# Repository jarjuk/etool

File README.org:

#+PROPERTY: header-args+ :var  ETOOL_DOCKER_TAG="9"
* marcus2002/etool - Docker mapping Gerber files to gcode with simulator support
:PROPERTIES:
:TOC:      :include all
:END:

 ~marcus2002/etool~ - a tool for mapping Gerber files, or image files,
 to gcode for CNC machining and for laser engraving. Provides [[https://linuxcnc.org/][linuxcnc]]
 -simulator for validating CNC execution paths.

:CONTENTS:
- [[#marcus2002etool---docker-mapping-gerber-files-to-gcode-with-simulator-support][marcus2002/etool - Docker mapping Gerber files to gcode with simulator support]]
  - [[#features][Features]]
  - [[#usage][Usage]]
  - [[#architecture][Architecture]]
  - [[#configuration-files-initialized-in-etool-directory][Configuration files initialized in etool directory]]
  - [[#installing-and-using--marcus2002etool][Installing and using  marcus2002/etool]]
    - [[#install-system-tools][Install system tools]]
      - [[#ubuntulinux][Ubuntu/Linux]]
      - [[#windows-10][Windows 10]]
      - [[#install-macos][Install MacOs]]
    - [[#pull-etool-docker-from-dockerio-repo][Pull etool Docker from docker.io repo]]
    - [[#running-etool][Running etool]]
  - [[#example-etool--workflow][Example etool -workflow]]
  - [[#default-cam-parameters][Default CAM parameters]]
    - [[#carving-cut-width-and-cut-depth][Carving cut width and cut depth]]
    - [[#carving-overlap][Carving overlap]]
  - [[#additional-cam-parameters][Additional CAM parameters]]
    - [[#3-grooves][3-grooves]]
  - [[#user-specific-cam-configuration][User specific CAM configuration]]
  - [[#example-projects][Example projects]]
  - [[#development][Development]]
  - [[#release--notes][RELEASE -notes]]
:END:

** Features

 - [X] Tools packaged into the Docker container
   - [X] [[https://github.com/pcb2gcode/pcb2gcode%20][pcb2gcode]] : Tool for mapping Gerber files to gcode
   - [X] [[https://www.linuxcnc.org/docs/2.4/html/gui_image-to-gcode.html][image-to-gcode]]: Tool to convert image to gcode
   - [X] [[https://linuxcnc.org/][linuxcnc]]: Simulator for validating CNC execution paths
   - [X] [[file:docker/etool/etool.sh][etool.sh]]: Simple bash script for managing configuration and
     diretory structures
 - [X] Workflow for processing gerbers
   - [X] Gerber input:
     - [X] Input example project Gerber files
     - [X] Accept project Gerber files from [[https://www.kicad.org/][Kicad EDA -tool]]
     - [X] Proviso for accepting project Gerber files from EDA tools using
       [[file:docker/etool/pcb2gcode-control.template][different naming scheme]]
   - [X] gerber -command
     - [X] converting project Gerger files to gcode
       - [X] [[file:docker/etool/pcb2gcode.ini][opinionated subset]] of ~pcb2gcode~ configurations for
         initialize configuration (possible to add other [[https://github.com/pcb2gcode/pcb2gcode/wiki][~pcb2gcode~ CLI
         configuration options]])
       - [X] set ~pcb2gcode~  autolevelling [on/off]
     - [X] converting Gerber files to png files for laser engraving
       - [X] Front and Back silk gerber layers converted to PNG -files
       - [X] Back silk images flopped around from  mirror position
   - [X] [[file:docker/etool/pcb2gcode-control.template][Gcode output]]:
     - [X] Front, Back, EdgeCut, PTH drill, NPTH drill -gcode files
     - [X] Scrit to create alignment drilling PTH-ALIGN.ngc from PTH.nfc
 - [X] Workflow for processing images
   - [X] Raster image (e.g. png)
   - [X] image -command mapping grey scale value 0..255 to gcode depth carving
 - [X] simulator -command for validating Gcode output
 - [X] Configuration management
   - [X] almost 'zero configuration' - requiring one empty, writable data directory
   - [X] directory structure and configurations automagically
     intialized in an empty data directory
   - [X] intialized configuration not overridden (=possible for user
     to modify initialized configuration)
   - [X] User specific CAM -configuration

** Usage

Command line usage
#+BEGIN_SRC bash :eval no-export :results output :results output :exports results
./etool.sh
#+END_SRC

#+RESULTS:
#+begin_example

         marcus2002/etool:9

         A tool for mapping Gerber/image files to gcode for CNC
         machining and launching linuxcnc -simulator for validating
         CNC execution paths.

         Usage:

         docker DOCKER_OPTS run marcus2002/etool CMD_AND_OPTIONS ...

         where CMD_AND_OPTIONS one of follwoing operations:
         o gerber PROJECT [USER] : create gcode for PROJECT Gerber -files into /etool/02-ngc -dir
                                   and png image files for laser engraving into /etool/02-silk -dir.
                                   USER -specific cam parameters replace default paramerters
                                   (/etool/pcb2gcode.ini, /etool/pcb2gcode-control.template)
         o adrill PROJECT        : convert PTH -drill file to alignement PTH-ALIGN drill file,
                                   used for two sided boards in /etool/02-ngc -dir
         o simulator             : start 'linuxcnc'

         or image cam operation:
         o image IMAGE           : convert IMAGE in /etool/01-image to gcode into /etool/02-ngc 

         or one of data management utilities:
         o ls                    : list data files in /etool -data directories
         o cleanup               : remove files from /etool -data directories
                                   /etool/01-gerber, /etool/01-image, /etool/02-ngc, and /etool/02-silk
         o example TYPE PROJECT  : copy example PROJECT of TYPE input directory
                                   TYPE is 'gerber' or 'image', with respective input direcotories
                                   01-gerber and 01-image

         or one of miscallaneous commands:
         o --help                : this help text
         o usage                 : workflow example (w. example of multiple commands on one line)
         o gerber-help           : help on pcb2gcode options to put into
                                   /etool/pcb2gcode.ini -file and open image explaining
                                   dimension options
         o releases              : output RELEASES document
         o Dockerfile            : show Dockerfile used

         and DOCKER_OPTS options for 'docker run' -command, particularly
         o --rm                             : cleanup after Docker finished
         o --user $(id -u):$(id -g)         : user credentials (instead of root)
         o -e DISPLAY=unix:0                : allow Docker to open X11 apps
         o -v /tmp/.X11-unix:/tmp/.X11-unix : allow Docker to open X11 apps
         o -v HOSTD:/etool                  : data directory HOSTD (must exist,
                                              owned by --user), structure is initialized
         
         Example usage:

         mkdir $HOME/.etool             # create working directory

         export ETOOL='docker run --rm --user 1000:1000 -e DISPLAY=unix:0 -v /tmp/.X11-unix:/tmp/.X11-unix -v $HOME/.etool:/etool marcus2002/etool:9'

         $ETOOL cleanup                 # clean working directories
         $ETOOL ls                      # empty directories
         $ETOOL example gerber soic     # init example 'soic'
         $ETOOL ls                      # expect to see directory /etool/01-gerber populated
         $ETOOL gerber soic             # create gCode for project 'soic'
         $ETOOL adrill soic             # create gcode for alignment create for project 'soic'
         $ETOOL simulator               # start linuxcnc for simulating gcode

         The commands can be given as a one-liner. For example, for the command above:

         $ETOOL cleanup ls example gerber soic ls gerber soic --  adrill soic simulator
         
         Notice! Separator '--' in cam -command signals end of optional parameters
#+end_example

** Architecture

Following box and line diagram gives an overview of ~marcus2002/etool~
-architecture. It presents,

1) *etool -directory*, in which docker ~marcus2002/etool~ initializes
   subdirectory structure and configurations. These configurations are
   accessed by the tools packaged within the container. Configuration
   files are documentend in the following chapter.

2) Gerber to gcode conversion

   1) Gerber files in *01-gerber* subdirectory. These files are
      created using plot command in KiCAD EDA -tool, or using
      ~example~ -command in ~marcus2002/etool~.

   2) Output produced with ~gerber~ -command in ~marcus2002/etool~:
      gcode files in *02-ngc* subdirectory.

   3) Output produced with ~gerber~ -command in ~marcus2002/etool~:
      png files for front and back Gerber -layers in *01-silk*
      subdirectory.

3) Image to gcode conversion

   1) Image files in *01-image* subdirectory. These files are created
      using drawing tool e.g. inkscape.

   2) Output produced with ~image~ -command in ~marcus2002/etool~: gcode
      files in *02-ngc* subdirectory.

4) gcode files in *02-ngc* -subdirectory read by ~linuxcnc~ -simulator
   packaged within in ~marcus2002/etool~ docker container.

5) gcode files in *02-ngc* -subdirectory copied for CNC for milling,
   drilling, and edge cutting.

6) Image files in *02-silk* -subdirectory copied for laser engraving

#+begin_example
                                     +--------------------------------+
                                     | marcus2002/etool -container    |
                                     | - pcb2gcode                    |
        +-----------------+          | - linuxcnc -simulator          |
        | EDA -tool e.g.  |          | - etool.sh -script             |
        | Kicad           |          | - initial configuration        |
        |                 |          +--------------------------------+
        +-----------------+               |     |       ^          ^
                   | +-----------------+  |     |       |          |
                   | | Drawing tool    |  |     |       |          |
                   | | e.g. inkscape   |  |     |       |          |
                   | |                 |  |     |       |          |
                   | +-----------------+  |     |       |          |
             plot  |    |                 |     |       |          |
          command  |    | +---------------+     |       |          |
                   |    | | example command     |       |tool      |
+----------------+ |    | |                init |       |access    | file read
|etool -directory| |    | |                once |       |          | for simulation
|                +-|-- -|-|---------------------|-------|---+      |
|   +--------------+    | |                     V       |   |      |
|   | +-----------------|-+                   configuration |      |
|   | |                 | |                                 |      |
|   | |   +-------------V-V-+        +-----------------+    |      |
|   | |   | 01-image        |        | 02-ngc          |    |      |
|   | |   |                 |  image |                 |-----------+
|   | |   | Image files     |--------> gcode -files    |    |   +-----------------+
|   | |   |                 |  +---->|                 |--------> CNC machine     |
|   | |   +-----------------+  |     +-----------------+    |   | - linuxcnc      |
|   | |                        |                            |   |                 |
|   | |                        |     +-----------------+    |   +-----------------+
| +-V-V-------------+          |     | 02-silk         |    |
| | 01-gerber       | gerber   |     |                 |    |   +-----------------+
| |                 |----------+-----> png -files      |    |   | Laser engraving |
| | Gerber files    |                |                 |------->|                 |
| |                 |                +-----------------+    |   |                 |
| +-----------------+                                       |   +-----------------+
|                                                           |
+-----------------------------------------------------------+

#+end_example

** Configuration files initialized in ~etool directory~

Following table summarizes configuration files initialized under
~etool~ -data directory.

| Configuration file               | Content                                                               |
|----------------------------------+-----------------------------------------------------------------------|
| [[file:docker/etool/pcb2gcode.ini]]  | pcb2gcode -tool CAM parameters  with instructions for 1/2 -sided PCBs |
| [[file:docker/etool/pcb2gcode-control.template][pcb2gcode-control.template]]       | Input/ouput configuration of pcb2gcode -tool                          |
| [[file:docker/etool/axis_etool.ini]] | linuxcnc simulator configuration (w. probe support)                   |

** Installing and using  ~marcus2002/etool~
:PROPERTIES:
:header-args:bash+: :dir  "."
:END:

*** Install system tools

**** Ubuntu/Linux

- Install Docker: https://docs.docker.com/engine/install/ubuntu/
- Post installation steps for Linux: https://docs.docker.com/engine/install/linux-postinstall/

**** Windows 10

- Install Docker Desktop on Windows: https://docs.docker.com/desktop/windows/install/
  - defines Windows features and Bios setting needed to run Docker
  - a hint for the impatient: installer checks that Docker
    prerequisites are met
- Install VcXsrv Windows X Server: https://sourceforge.net/projects/vcxsrv/
  - When launching VcXsrv choose 'disable access control checked' to
    allow Docker to open X11 windows

*Windows 10 problems*:
- linuxcnc simulator machinen preview did not work. Patched
  [[file:etool.cmd]] to set environment variable
  ~LIBGL_ALWAYS_INDIRECT=1~. In spite of this "fix" need to click DRO
  tab to make linuxcnc to refresh machine preview.

**** Install MacOs

- Install Docker Desktop on Mac: https://docs.docker.com/desktop/mac/install/
- Install X11 support on Mac: https://www.xquartz.org/

*MacOs X11 problem*:

Xquartz 2.8.1 may report an error
#+begin_example
libGL error: No matching fbConfigs or visuals found
libGL error: failed to load driver: swrast
#+end_example
which may be solved issuing command
#+begin_example
defaults write org.xquartz.X11 enable_iglx -bool true
#+end_example
and restarting XQuartz again. However, it may be this does not fix the
problem persistently, and XQuartz must be restarted again, after each
X11 session launch.

*** Pull ~etool~ Docker from docker.io repo

Current Docker Tag
#+BEGIN_SRC bash :eval no-export :results output :exports results
echo ETOOL_DOCKER_TAG=$ETOOL_DOCKER_TAG
#+END_SRC

#+RESULTS:
: ETOOL_DOCKER_TAG=9

Pull ~marcus2002/etool:$ETOOL_DOCKER_TAG~ from Docker hub

#+BEGIN_SRC bash :eval no-export :results output :exports both
docker pull marcus2002/etool:$ETOOL_DOCKER_TAG
#+END_SRC

: 9: Pulling from marcus2002/etool
: Digest: sha256:514c385deede32a71bf4e57752d28bf72b0cfdee7802237a1ebd98f3b83d2d6b
: Status: Image is up to date for marcus2002/etool:9
: docker.io/marcus2002/etool:9

: Digest: sha256:8150eb52eb17bf79acf92d8f47bf5e9ff7e0e46fb0d69fa704446388efeb36ee
: Status: Image is up to date for marcus2002/etool:7
: docker.io/marcus2002/etool:7

*** Running etool

To simplify running  ~marcus2002/etool~ two scripts are provided

- [[file:etool.sh]] : Running ~marcus2002/etool~ on Linux
- [[file:etoolMac.sh]] : Running ~marcus2002/etool~ on MacOs
- [[file:etool.cmd]] : Running ~marcus2002/etool~  on Windows

Copy these scripts to a CLI PATH and validate ETOOL_DIR and TAG
variables (change if needed). Validate installation and version with
the command

#+BEGIN_SRC bash :eval no-export :results output :exports both
./etool.sh --version
#+END_SRC

#+RESULTS:
:          marcus2002/etool:7

** Example ~etool~ -workflow

Using data directory ~tmp/etool~ for tesing. Reset directory and
remove old existing directory
#+BEGIN_SRC bash :eval no-export :results output
rm -rf tmp/etool
mkdir -p tmp/etool
#+END_SRC

#+RESULTS:

Use ~<<run-etool>>~ below as a short hand for
#+name: run-etool
#+BEGIN_SRC bash :eval no :results output :exports code
docker run --rm --user $(id -u):$(id -g) -e DISPLAY=unix:0 -v /tmp/.X11-unix:/tmp/.X11-unix -v $(pwd)/tmp/etool:/etool marcus2002/etool:$ETOOL_DOCKER_TAG
#+END_SRC

Calling ~<<run-etool>>~ for the first time inializes directory
structure. Command ~ls~ shows empty directories ~/etool/01-gerber~, 
~/etool/02-ngc~, and ~/etool/02-silk~:

#+BEGIN_SRC bash :eval no-export :results output :noweb yes :exports both
<<run-etool>> ls
#+END_SRC

#+RESULTS:
#+begin_example
Directory /etool/01-gerber created
Directory /etool/01-image created
Directory /etool/02-ngc created
Directory /etool/02-silk created
Directory /etool/linuxcnc/configs/sim.axis created
File /etool/pcb2gcode.ini created
File /etool/linuxcnc/configs/sim.axis/axis_etool.ini created
File /etool/linuxcnc/configs/sim.axis/sim_mm.tbl created
File /etool/pcb2gcode-control.template created
File /etool/.linuxcncrc created
/etool/01-gerber:
total 0

/etool/01-image:
total 0

/etool/02-ngc:
total 0

/etool/02-silk:
total 0
#+end_example

Use ~<<run-etool>>~ to populate example Gerbers for ~soic~ -project:

#+BEGIN_SRC bash :eval no-export :results output :noweb yes :exports both
<<run-etool>> example gerber soic
#+END_SRC

#+RESULTS:
#+begin_example
Directory /etool/01-gerber exits - not modified
Directory /etool/01-image exits - not modified
Directory /etool/02-ngc exits - not modified
Directory /etool/02-silk exits - not modified
Directory /etool/linuxcnc/configs/sim.axis exits - not modified
File /etool/pcb2gcode.ini exits - not modified
File /etool/linuxcnc/configs/sim.axis/axis_etool.ini exits - not modified
File /etool/linuxcnc/configs/sim.axis/sim_mm.tbl exits - not modified
File /etool/pcb2gcode-control.template exits - not modified
File /etool/.linuxcncrc exits - not modified
soic-B_Cu.gbr
soic-B_Mask.gbr
soic-B_Paste.gbr
soic-B_SilkS.gbr
soic-Edge_Cuts.gbr
soic-F_Cu.gbr
soic-F_Mask.gbr
soic-F_Paste.gbr
soic-F_SilkS.gbr
soic-NPTH-drl_map.ps
soic-NPTH.drl
soic-PTH-drl_map.ps
soic-PTH.drl
soic-job.gbrjob
#+end_example

Using ~gerber~-command in ~<<run-etool>>~ for ~soic~ -project to
create gcode files into ~02-ngc~ directory, and png files into
~02-silk~ directory

#+BEGIN_SRC bash :eval no-export :results output :noweb yes :exports both
<<run-etool>> gerber soic
#+END_SRC

#+RESULTS:
#+begin_example
Directory /etool/01-gerber exits - not modified
Directory /etool/01-image exits - not modified
Directory /etool/02-ngc exits - not modified
Directory /etool/02-silk exits - not modified
Directory /etool/linuxcnc/configs/sim.axis exits - not modified
File /etool/pcb2gcode.ini exits - not modified
File /etool/linuxcnc/configs/sim.axis/axis_etool.ini exits - not modified
File /etool/linuxcnc/configs/sim.axis/sim_mm.tbl exits - not modified
File /etool/pcb2gcode-control.template exits - not modified
File /etool/.linuxcncrc exits - not modified
pcb2gcode using configuration files /etool/pcb2gcode-control.template, /etool/pcb2gcode.ini
Importing front side... DONE.
Importing back side... DONE.
Importing outline... DONE.
Processing input files... DONE.
Exporting back... DONE. (Height: 15.1mm Width: 34.1mm)
Exporting front... DONE. (Height: 15.1mm Width: 34.1mm)
Exporting outline... DONE. (Height: 15.1mm Width: 34.1mm) The board should be cut from the FRONT side. 
Importing drill... DONE.
Exporting milldrill... Exporting drill... DONE. The board should be drilled from the FRONT side.
END.
Importing front side... not specified.
Importing back side... not specified.
Importing outline... DONE.
Processing input files... DONE.
Exporting outline... DONE. (Height: 15.1mm Width: 34.1mm) The board should be cut from the FRONT side. 
Importing drill... DONE.
Exporting milldrill... Exporting drill... DONE. The board should be drilled from the FRONT side.
END.
Convert Gerber  /etool/01-gerber/soic-F_SilkS.gbr to png -image /etool/02-silk/soic-F_SilkS.png
Convert Gerber  /etool/01-gerber/soic-B_SilkS.gbr to png -image /etool/02-silk/soic-B_SilkS.png
#+end_example

After ~cam~ command, directory ~/etool/02-ngc~ contains gcode in ~ngc~
-files, and directory ~/etool/02-silk~ ~png~ -files for gerber silk
layers:

#+BEGIN_SRC bash :eval no-export :results output :noweb yes :exports both
<<run-etool>> ls
#+END_SRC

#+RESULTS:
#+begin_example
Directory /etool/01-gerber exits - not modified
Directory /etool/01-image exits - not modified
Directory /etool/02-ngc exits - not modified
Directory /etool/02-silk exits - not modified
Directory /etool/linuxcnc/configs/sim.axis exits - not modified
File /etool/pcb2gcode.ini exits - not modified
File /etool/linuxcnc/configs/sim.axis/axis_etool.ini exits - not modified
File /etool/linuxcnc/configs/sim.axis/sim_mm.tbl exits - not modified
File /etool/pcb2gcode-control.template exits - not modified
File /etool/.linuxcncrc exits - not modified
/etool/01-gerber:
total 112
-rw-r--r-- 1 1000 1000  1953 Jul  4 11:11 soic-B_Cu.gbr
-rw-r--r-- 1 1000 1000  1035 Jul  4 11:11 soic-B_Mask.gbr
-rw-r--r-- 1 1000 1000   541 Jul  4 11:11 soic-B_Paste.gbr
-rw-r--r-- 1 1000 1000 12476 Jul  4 11:11 soic-B_SilkS.gbr
-rw-r--r-- 1 1000 1000   749 Jul  4 11:11 soic-Edge_Cuts.gbr
-rw-r--r-- 1 1000 1000  5874 Jul  4 11:11 soic-F_Cu.gbr
-rw-r--r-- 1 1000 1000  3504 Jul  4 11:11 soic-F_Mask.gbr
-rw-r--r-- 1 1000 1000  3010 Jul  4 11:11 soic-F_Paste.gbr
-rw-r--r-- 1 1000 1000  5682 Jul  4 11:11 soic-F_SilkS.gbr
-rw-r--r-- 1 1000 1000 15377 Jul  4 11:11 soic-NPTH-drl_map.ps
-rw-r--r-- 1 1000 1000   377 Jul  4 11:11 soic-NPTH.drl
-rw-r--r-- 1 1000 1000 27525 Jul  4 11:11 soic-PTH-drl_map.ps
-rw-r--r-- 1 1000 1000   532 Jul  4 11:11 soic-PTH.drl
-rw-r--r-- 1 1000 1000  2491 Jul  4 11:11 soic-job.gbrjob

/etool/01-image:
total 0

/etool/02-ngc:
total 624
-rw-r--r-- 1 1000 1000    412 Jul  4 11:12 original_drill.svg
-rw-r--r-- 1 1000 1000   5311 Jul  4 11:12 outp0_original_back.svg
-rw-r--r-- 1 1000 1000    522 Jul  4 11:12 outp0_original_outline.svg
-rw-r--r-- 1 1000 1000  10814 Jul  4 11:12 outp1_original_front.svg
-rw-r--r-- 1 1000 1000    522 Jul  4 11:12 outp2_original_outline.svg
-rw-r--r-- 1 1000 1000   5312 Jul  4 11:12 outp3_masked_back.svg
-rw-r--r-- 1 1000 1000  10817 Jul  4 11:12 outp4_masked_front.svg
-rw-r--r-- 1 1000 1000  61090 Jul  4 11:12 processed_back.svg
-rw-r--r-- 1 1000 1000  37018 Jul  4 11:12 processed_back_final.svg
-rw-r--r-- 1 1000 1000 109965 Jul  4 11:12 processed_front.svg
-rw-r--r-- 1 1000 1000  68915 Jul  4 11:12 processed_front_final.svg
-rw-r--r-- 1 1000 1000   2192 Jul  4 11:12 processed_outline.svg
-rw-r--r-- 1 1000 1000  29533 Jul  4 11:12 soic-B_Cu.ngc
-rw-r--r-- 1 1000 1000   3707 Jul  4 11:12 soic-Edge_Cuts.ngc
-rw-r--r-- 1 1000 1000  50897 Jul  4 11:12 soic-F_Cu.ngc
-rw-r--r-- 1 1000 1000    737 Jul  4 11:12 soic-NPTH.ngc
-rw-r--r-- 1 1000 1000    902 Jul  4 11:12 soic-PTH.ngc
-rw-r--r-- 1 1000 1000  45335 Jul  4 11:12 traced_back.svg
-rw-r--r-- 1 1000 1000  21263 Jul  4 11:12 traced_back_final.svg
-rw-r--r-- 1 1000 1000  79633 Jul  4 11:12 traced_front.svg
-rw-r--r-- 1 1000 1000  38583 Jul  4 11:12 traced_front_final.svg
-rw-r--r-- 1 1000 1000   1770 Jul  4 11:12 traced_outline.svg

/etool/02-silk:
total 12
-rw-r--r-- 1 1000 1000 4744 Jul  4 11:12 soic-B_SilkS.png
-rw-r--r-- 1 1000 1000 3437 Jul  4 11:12 soic-F_SilkS.png
#+end_example

Soic -project uses two sided PCB layout. To align board in milling,
the PCB design is symmetrical along Y-axis with origin on lower edge
of the PCB board. The design contains two alignement vias on the
Y-axis. First via is in position (0mm,-3mm) and the second is located
on the Y-axis, 3mm above the board top edge on Y=14mm. These vias are
drilled to -4.5mm *into the supporting plane* (= use thick enough
sacrifial plane where PCB is attached to avoid drilling into CNC
table).

The crux of this drilling operation is gcode snippet shown below

#+begin_example
G81 R2.00000  Z-4.5000  F30.00000 X0.00000 Y-3.0000
X0.00000 Y14.00000
G80
#+end_example

To create alignement drilling ~<<run-etool>>~ provides command
~adrill~. 

For example, to create ~PTH-ALIGN.ngc~ for soic project run:

#+BEGIN_SRC bash :eval no-export :results output :noweb yes :exports both
<<run-etool>> adrill soic
#+END_SRC

#+RESULTS:
: PTH_DRILL=/etool/02-ngc/soic-PTH.ngc, ALIGN_DRILL=/etool/02-ngc/soic-PTH-ALIGN.ngc

Command ~ls~ shows new file ~soic-PTH-ALIGN.ngc~ in directory ~02-ngc~:
#+BEGIN_SRC bash :eval no-export :results output :noweb yes :exports both
  <<run-etool>> ls
#+END_SRC

#+RESULTS:
#+begin_example
Directory /etool/01-gerber exits - not modified
Directory /etool/01-image exits - not modified
Directory /etool/02-ngc exits - not modified
Directory /etool/02-silk exits - not modified
Directory /etool/linuxcnc/configs/sim.axis exits - not modified
File /etool/pcb2gcode.ini exits - not modified
File /etool/linuxcnc/configs/sim.axis/axis_etool.ini exits - not modified
File /etool/linuxcnc/configs/sim.axis/sim_mm.tbl exits - not modified
File /etool/pcb2gcode-control.template exits - not modified
File /etool/.linuxcncrc exits - not modified
/etool/01-gerber:
total 112
-rw-r--r-- 1 1000 1000  1953 Jul  4 11:11 soic-B_Cu.gbr
-rw-r--r-- 1 1000 1000  1035 Jul  4 11:11 soic-B_Mask.gbr
-rw-r--r-- 1 1000 1000   541 Jul  4 11:11 soic-B_Paste.gbr
-rw-r--r-- 1 1000 1000 12476 Jul  4 11:11 soic-B_SilkS.gbr
-rw-r--r-- 1 1000 1000   749 Jul  4 11:11 soic-Edge_Cuts.gbr
-rw-r--r-- 1 1000 1000  5874 Jul  4 11:11 soic-F_Cu.gbr
-rw-r--r-- 1 1000 1000  3504 Jul  4 11:11 soic-F_Mask.gbr
-rw-r--r-- 1 1000 1000  3010 Jul  4 11:11 soic-F_Paste.gbr
-rw-r--r-- 1 1000 1000  5682 Jul  4 11:11 soic-F_SilkS.gbr
-rw-r--r-- 1 1000 1000 15377 Jul  4 11:11 soic-NPTH-drl_map.ps
-rw-r--r-- 1 1000 1000   377 Jul  4 11:11 soic-NPTH.drl
-rw-r--r-- 1 1000 1000 27525 Jul  4 11:11 soic-PTH-drl_map.ps
-rw-r--r-- 1 1000 1000   532 Jul  4 11:11 soic-PTH.drl
-rw-r--r-- 1 1000 1000  2491 Jul  4 11:11 soic-job.gbrjob

/etool/01-image:
total 0

/etool/02-ngc:
total 628
-rw-r--r-- 1 1000 1000    412 Jul  4 11:12 original_drill.svg
-rw-r--r-- 1 1000 1000   5311 Jul  4 11:12 outp0_original_back.svg
-rw-r--r-- 1 1000 1000    522 Jul  4 11:12 outp0_original_outline.svg
-rw-r--r-- 1 1000 1000  10814 Jul  4 11:12 outp1_original_front.svg
-rw-r--r-- 1 1000 1000    522 Jul  4 11:12 outp2_original_outline.svg
-rw-r--r-- 1 1000 1000   5312 Jul  4 11:12 outp3_masked_back.svg
-rw-r--r-- 1 1000 1000  10817 Jul  4 11:12 outp4_masked_front.svg
-rw-r--r-- 1 1000 1000  61090 Jul  4 11:12 processed_back.svg
-rw-r--r-- 1 1000 1000  37018 Jul  4 11:12 processed_back_final.svg
-rw-r--r-- 1 1000 1000 109965 Jul  4 11:12 processed_front.svg
-rw-r--r-- 1 1000 1000  68915 Jul  4 11:12 processed_front_final.svg
-rw-r--r-- 1 1000 1000   2192 Jul  4 11:12 processed_outline.svg
-rw-r--r-- 1 1000 1000  29533 Jul  4 11:12 soic-B_Cu.ngc
-rw-r--r-- 1 1000 1000   3707 Jul  4 11:12 soic-Edge_Cuts.ngc
-rw-r--r-- 1 1000 1000  50897 Jul  4 11:12 soic-F_Cu.ngc
-rw-r--r-- 1 1000 1000    737 Jul  4 11:12 soic-NPTH.ngc
-rw-r--r-- 1 1000 1000   1158 Jul  4 11:15 soic-PTH-ALIGN.ngc
-rw-r--r-- 1 1000 1000    902 Jul  4 11:12 soic-PTH.ngc
-rw-r--r-- 1 1000 1000  45335 Jul  4 11:12 traced_back.svg
-rw-r--r-- 1 1000 1000  21263 Jul  4 11:12 traced_back_final.svg
-rw-r--r-- 1 1000 1000  79633 Jul  4 11:12 traced_front.svg
-rw-r--r-- 1 1000 1000  38583 Jul  4 11:12 traced_front_final.svg
-rw-r--r-- 1 1000 1000   1770 Jul  4 11:12 traced_outline.svg

/etool/02-silk:
total 12
-rw-r--r-- 1 1000 1000 4744 Jul  4 11:12 soic-B_SilkS.png
-rw-r--r-- 1 1000 1000 3437 Jul  4 11:12 soic-F_SilkS.png
#+end_example

Use ~simulator~ command to start linuxcnc simulator. Especially,
validate gcode in ~PTH-ALIGN.ngc~ file.

Running

#+BEGIN_SRC bash :eval no-export :results output :noweb yes :exports code
<<run-etool>> simulator
#+END_SRC

#+RESULTS:
: Directory /etool/01-gerber exits - not modified
: Directory /etool/02-ngc exits - not modified
: Directory /etool/linuxcnc/configs/sim.axis exits - not modified
: File /etool/pcb2gcode.ini exits - not modified
: File /etool/linuxcnc/configs/sim.axis/axis_etool.ini exits - not modified
: File /etool/linuxcnc/configs/sim.axis/sim_mm.tbl exits - not modified
: File /etool/pcb2gcode-control.template exits - not modified
: File /etool/.linuxcncrc exits - not modified
: RUN: linuxcnc

opens dialog for configuration selection (Choose ~axis_etool~)

[[file:pics-keep/simulator-conf.png]]

~linuxcnc~ ~File Open~ -command shows gcode files in ~/etool/02-ngc~
-directory

[[file:pics-keep/simulator-open-file.png]]

Finally, ~cleanup~ -command empties data directories, and ~ls~
-command shows that data directories ~/etool/01-gerber~ and
~/etool/02-ngc~ are empty.
#+BEGIN_SRC bash :eval no-export :results output :noweb yes :exports both
<<run-etool>> cleanup ls
#+END_SRC

#+RESULTS:
#+begin_example
Directory /etool/01-gerber exits - not modified
Directory /etool/01-image exits - not modified
Directory /etool/02-ngc exits - not modified
Directory /etool/02-silk exits - not modified
Directory /etool/linuxcnc/configs/sim.axis exits - not modified
File /etool/pcb2gcode.ini exits - not modified
File /etool/linuxcnc/configs/sim.axis/axis_etool.ini exits - not modified
File /etool/linuxcnc/configs/sim.axis/sim_mm.tbl exits - not modified
File /etool/pcb2gcode-control.template exits - not modified
File /etool/.linuxcncrc exits - not modified
/etool/01-gerber:

/etool/01-image:
/etool/01-gerber:
total 0

/etool/01-image:
total 0

/etool/02-ngc:
total 0

/etool/02-silk:
total 0
#+end_example

** Default CAM parameters

*** Carving cut width and cut depth

 #+caption: V -milling bit
 [[file:pics-keep/v-bit2.png]]

 Figure 1 shows geometry for a V -milling bit with tip width ~w~ and
 tip angle ~\alpha~. When using engraving depth ~z~, the resulting
 groove has width of ~cut~.

 #+caption: V -milling bit
 [[file:pics-keep/latex-calc.png]]

 Python script for calculating cut width for V -milling bit with tip
 width ~w~, tip angle ~alpha~, and carving depth ~z~

 #+BEGIN_SRC python :eval no-export :results output :noweb no :session *Python* :exports code
 from  math import tan, radians
 def cutWidth( alpha, w, z):
    cut = 2*tan(radians(alpha)/2)*(w/2/tan(radians(alpha)/2) + z)
    return cut
 #+END_SRC

Using the script above to calculate cut width for V -milling bit
 - with tip angle ~alpha=60 deg~
 - and tip width ~w=0.1 mm~
 - carving into depth ~z=0.1 mm~

 #+name: example1
 #+BEGIN_SRC python :eval no-export :results output :noweb no :session *Python* :exports both
 print( f"cut={cutWidth(alpha=60,w=0.1,z=.1):.4f}")
 #+END_SRC

returns ~cut~ witdh

 #+RESULTS: example1
 : cut=0.2155

Default CAM configuration [[file:docker/etool/pcb2gcode.ini]] defines
carving parameters:

#+BEGIN_SRC bash :eval no-export :results output :exports results
grep -E '^mill-diameters|^zwork' docker/etool/pcb2gcode.ini
#+END_SRC

#+RESULTS:
: zwork=-0.1mm            # milling depth
: mill-diameters=0.2155mm # milling cut

*** Carving overlap

Python script to calculate minimum overlap -% needed to achieve
isolation width $i$ when carving $n$ grooves of width $cut$:

#+BEGIN_SRC python :eval no-export :results output :noweb no :session *Python* :exports code
  def overLap( i, cut, n):
      """:return: (min) overLap -‰ needed to achive isolation 'i' when
      carving 'n' grooves of width 'cut'. None if not possible

      """
      # Max area possible to cover with n cuts
      maxCarvingCover = n*cut

      # Not possible to isolate
      if maxCarvingCover < i: return None

      # Need at least two carvings to have any overLap
      if n < 2: return None
      
      #  width of one overLap 
      overLapWidth = (maxCarvingCover - i)/(n-1)
      
      # one overLap width from cut width as percent
      return overLapWidth / cut * 100.0
#+END_SRC

#+RESULTS:

To achive isolation width ~0.38mm~, when carving ~2~ grooves of width
~0.2155mm~ requires
#+name: example2
#+BEGIN_SRC python :eval no-export :results output :noweb no :session *Python* :exports results
  print( f"{overLap(i=0.38, cut=0.2155, n=2):.1f}%")
#+END_SRC

overlap ‰ 

#+RESULTS: example2
: 23.7%

Default CAM configuration [[file:docker/etool/pcb2gcode.ini]] defines cut
width, isolation width, and overlap percent as shown below

#+BEGIN_SRC bash :eval no-export :results output :exports results
grep -E '^mill-diameters|^isolation-width|^milling-overlap' docker/etool/pcb2gcode.ini
#+END_SRC

#+RESULTS:
: isolation-width=0.38mm # min width between copper surfaces
: mill-diameters=0.2155mm # milling cut
: milling-overlap=23%     # overlap milling passes, [%/mm]

** Additional CAM parameters

*** 3-grooves
:PROPERTIES:
:header-args+: :var  USER_CONFIG="3-grooves"
:header-args+: :var  ISOLATION_WIDTH=0.38
:header-args+: :var  MILL_DIAMETERS=0.2155
:header-args+: :var  MILLING_OVERLAP=60
:header-args+: :dir  "docker/etool"
:END:

~3-grooves~ -CAM configruation uses three passes to isolate tracks on
PCB. 

#+name: 3-grooves
#+BEGIN_SRC python :eval no-export :results output :noweb no :session *Python* :exports results
  n = 3
  print( f"To achive isolation width {ISOLATION_WIDTH}, when carving {n} cuts")
  print( f"using milling bit with cutting width of {MILL_DIAMETERS} mm")
  print( f"requires overlap of {overLap(i=ISOLATION_WIDTH, cut=MILL_DIAMETERS, n=n):.1f}%")
#+END_SRC

#+RESULTS: 3-grooves
: To achive isolation width 0.38, when carving 3 cuts
: using milling bit with cutting width of 0.2155 mm
: requires overlap of 61.8%

#+BEGIN_SRC bash :eval no-export :results output :exports none
# Generate automagicaly USER_CONFIG
cp pcb2gcode.ini pcb2gcode-${USER_CONFIG}.ini
cp pcb2gcode-control.template pcb2gcode-control-${USER_CONFIG}.template 
sed  -i -E "s/^isolation-width=[0-9.]+/isolation-width=${ISOLATION_WIDTH}/" pcb2gcode-${USER_CONFIG}.ini
sed  -i -E "s/^milling-overlap=[0-9.]+/milling-overlap=${MILLING_OVERLAP}/" pcb2gcode-${USER_CONFIG}.ini
# Modify configurations
#+END_SRC

#+RESULTS:

CAM configuration [[file:docker/etool/pcb2gcode-3-grooves.ini]] defines cut
width, isolation width, and overlap percent as shown below

#+BEGIN_SRC bash :eval no-export :results output :exports results
grep -E '^mill-diameters|^isolation-width|^milling-overlap' pcb2gcode-${USER_CONFIG}.ini
#+END_SRC

#+RESULTS:
: isolation-width=0.38mm # min width between copper surfaces
: mill-diameters=0.2155mm # milling cut
: milling-overlap=60%     # overlap milling passes, [%/mm]

** User specific CAM configuration

Docker finds configuration files for ~pcb2gcode~ CAM -tool in ~/etool~
directory mapped to a host directory in ~docker run~ -command. For
example, this README uses following command

#+BEGIN_SRC bash :eval no-export :results output :noweb yes :exports results
echo '<<run-etool>>'
#+END_SRC

#+RESULTS:
: docker run --rm --user $(id -u):$(id -g) -e DISPLAY=unix:0 -v /tmp/.X11-unix:/tmp/.X11-unix -v $(pwd)/tmp/etool:/etool marcus2002/etool:$ETOOL_DOCKER_TAG

In this case, host directory is ~$(pwd)/tmp/etool~, and its directory
listing shows default configuration files ~pcb2gcode.ini~ and
~pcb2gcode-control.template~

#+BEGIN_SRC bash :eval no-export :results output :exports both
ls $(pwd)/tmp/etool
#+END_SRC

#+RESULTS:
: 01-gerber
: 01-image
: 02-ngc
: linuxcnc
: pcb2gcode-control.template
: pcb2gcode.ini

To create user specific configuration files copy these files to
~pcb2gcode-${USR}.ini~ and ~pcb2gcode-control-$USR.template~. For
example to create user specific configuration files USER1 issue
commands, and edit newly created files at will.

#+BEGIN_SRC bash :eval no-export :results output
USR=USER1
cp $(pwd)/tmp/etool/pcb2gcode.ini  $(pwd)/tmp/etool/pcb2gcode-${USR}.ini
cp $(pwd)/tmp/etool/pcb2gcode-control.template  $(pwd)/tmp/etool/pcb2gcode-control-$USR.template
#+END_SRC

#+RESULTS:

After the copy, content of directory  ~$(pwd)/tmp/etool~

#+BEGIN_SRC bash :eval no-export :results output :exports results
ls $(pwd)/tmp/etool
#+END_SRC

#+RESULTS:
: 01-gerber
: 01-image
: 02-ngc
: linuxcnc
: pcb2gcode-control.template
: pcb2gcode-control-USER1.template
: pcb2gcode.ini
: pcb2gcode-USER1.ini

and cam -command can access the user specific configuration files:

#+BEGIN_SRC bash :eval no-export :results output :noweb yes :exports both
<<run-etool>> example gerber pad2pad gerber pad2pad USER1
#+END_SRC

#+RESULTS:
#+begin_example
Directory /etool/01-gerber exits - not modified
Directory /etool/01-image exits - not modified
Directory /etool/02-ngc exits - not modified
Directory /etool/linuxcnc/configs/sim.axis exits - not modified
File /etool/pcb2gcode.ini exits - not modified
File /etool/linuxcnc/configs/sim.axis/axis_etool.ini exits - not modified
File /etool/linuxcnc/configs/sim.axis/sim_mm.tbl exits - not modified
File /etool/pcb2gcode-control.template exits - not modified
File /etool/.linuxcncrc exits - not modified
pad2pad-B_Cu.gbr
pad2pad-B_Mask.gbr
pad2pad-B_Paste.gbr
pad2pad-B_SilkS.gbr
pad2pad-Edge_Cuts.gbr
pad2pad-F_Cu.gbr
pad2pad-F_Mask.gbr
pad2pad-F_Paste.gbr
pad2pad-F_SilkS.gbr
pad2pad-NPTH-drl_map.ps
pad2pad-NPTH.drl
pad2pad-PTH-drl_map.ps
pad2pad-PTH.drl
pad2pad-job.gbrjob
pcb2gcode using configuration files /etool/pcb2gcode-control-USER1.template, /etool/pcb2gcode-USER1.ini
Importing front side... DONE.
Importing back side... DONE.
Importing outline... DONE.
Processing input files... DONE.
Exporting back... DONE. (Height: 11.85mm Width: 19.6mm)
Exporting front... DONE. (Height: 11.85mm Width: 19.6mm)
Exporting outline... DONE. (Height: 11.85mm Width: 19.6mm) The board should be cut from the FRONT side.
Importing drill... DONE.
Exporting milldrill... Exporting drill... DONE. The board should be drilled from the FRONT side.
END.
Importing front side... not specified.
Importing back side... not specified.
Importing outline... DONE.
Processing input files... DONE.
Exporting outline... DONE. (Height: 11.85mm Width: 19.6mm) The board should be cut from the FRONT side.
Importing drill... DONE.
Exporting milldrill... Exporting drill... DONE. The board should be drilled from the FRONT side.
END.
#+end_example

Notice, how the output above refers to configuration files
~/etool/pcb2gcode-control-USER1.template~ and
~/etool/pcb2gcode-USER1.ini~.

** Example projects

The tool includes following example gerbers projects:
- ~pad2pad~
  - Resistor, Led size 0805
  - Edge Cut: 10x10 mm
  - pin-header, 2.54 grid
  - grid 2.54 mm
  - track width 0.5 mm
  - 0,0 is lower left corner
  - one sided, F_Cu
- ~dip~
  - Bottom Left corner (X,Y)=(0,0)
  - Edge Cut: 40x20 mm
  - Fab: board dimension
  - track width 0.5mm (B_Cu)
  - 2x pin-header 1x4, 1.27mm grid, (PTH-drilling)
  - DIP8 package
  - one sided, B_Cu
  - Front silk:
    - silk text width/height/thickness: 1.5/1.5/0.2
    - edge markers on board cuts
- ~soic~
  - two sided 30 mm x 11 mm
     - 2 x Alignement vias
     - front copper track 0.25 (F_Cu)
     - front silk text w. edge markers
     - back copper track 0.25 (B_Cu)
     - back silk (=mirrored) text w. edge markers
     - 0.25 mm track passing between soic pads
  - 2 x 0603 pad
  - 2 x Mounting hole 2.5 mm (NPTH)
  - Pin header 1x4, 1.27 mm
  - 1 via between F_Cu/B_Cu
  - Pin header 1x4, 2 mm
  - SOIC8 package (F_Cu)

The tool includes following example images for demonstrating ~image~
command:
- ~hello.eps~
  - 9 x 25 mm black and white text Hello
- ~sign.png~
  - 857 x 854 px 50 km/h traffic sign

** Development

Ref: [[file:docker.org]]

** RELEASE -notes

Ref: [[file:docker/etool/RELEASES]]

* Fin                                                              :noexport:

   #+RESULTS:

   # Local Variables:
   # org-confirm-babel-evaluate: nil
   # org-make-toc-mode: t
   # End:

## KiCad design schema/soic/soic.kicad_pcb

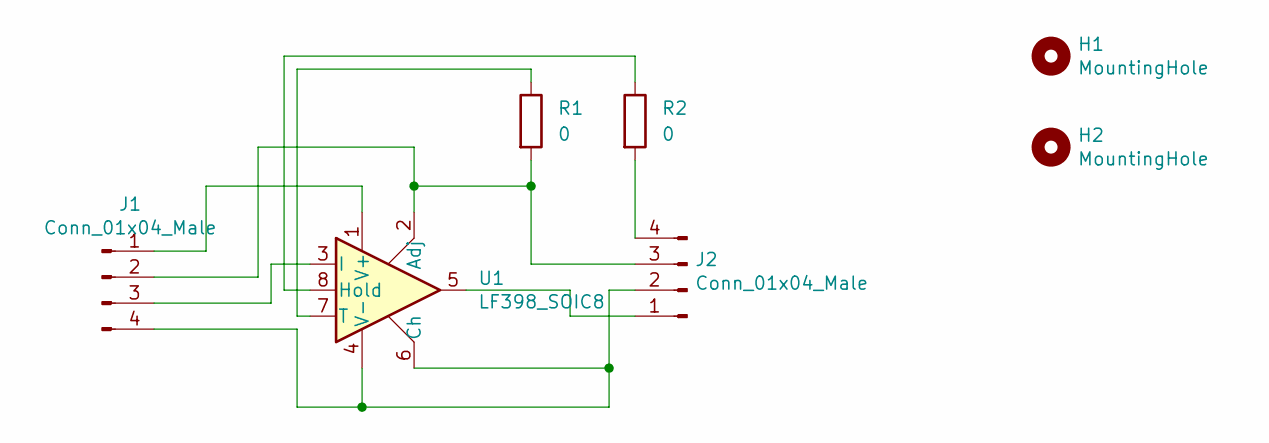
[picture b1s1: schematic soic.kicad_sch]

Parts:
H1, H2: MountingHole; MountingHole_2.5mm
J1: Conn_01x04_Male; PinHeader_1x04_P1.27mm_Vertical
J2: Conn_01x04_Male
R1, R2: 0
U1: LF398_SOIC8; SOIC-8_3.9x4.9mm_P1.27mm

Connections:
unnamed: J1.1, U1.1 (V+)
unnamed: J1.2, J2.3, R1.2, U1.2 (Adj)
unnamed: J1.3, U1.3 (I)
unnamed: J1.4, J2.2, U1.4 (V-), U1.6 (Ch)
unnamed: J2.1, U1.5
unnamed: J2.4, R2.2
unnamed: R1.1, U1.7 (T)
unnamed: R2.1, U1.8 (Hold)

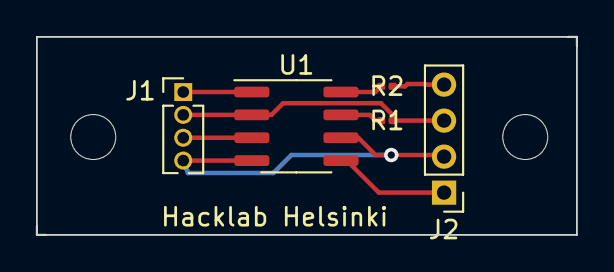
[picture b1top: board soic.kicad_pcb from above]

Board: 2 copper layers, 30.0 x 11.0 mm, 7 parts (0 on the bottom side), 8 nets.

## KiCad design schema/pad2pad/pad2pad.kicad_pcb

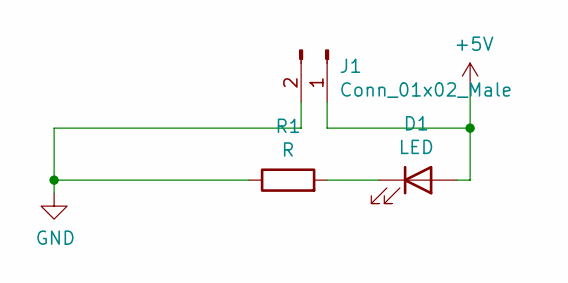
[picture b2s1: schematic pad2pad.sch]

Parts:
D1: LED; LED_0805_2012Metric
J1: Conn_01x02_Male; PinHeader_1x02_P2.54mm_Vertical
R1: R; R_0805_2012Metric

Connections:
+5V: D1.2 (A), J1.1
GND: J1.2, R1.1
unnamed: D1.1 (K), R1.2

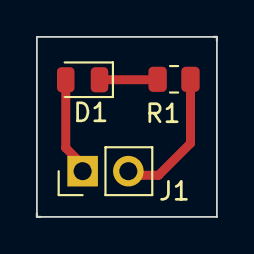
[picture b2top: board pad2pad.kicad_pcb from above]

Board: 2 copper layers, 10.0 x 10.0 mm, 3 parts (0 on the bottom side), 3 nets.

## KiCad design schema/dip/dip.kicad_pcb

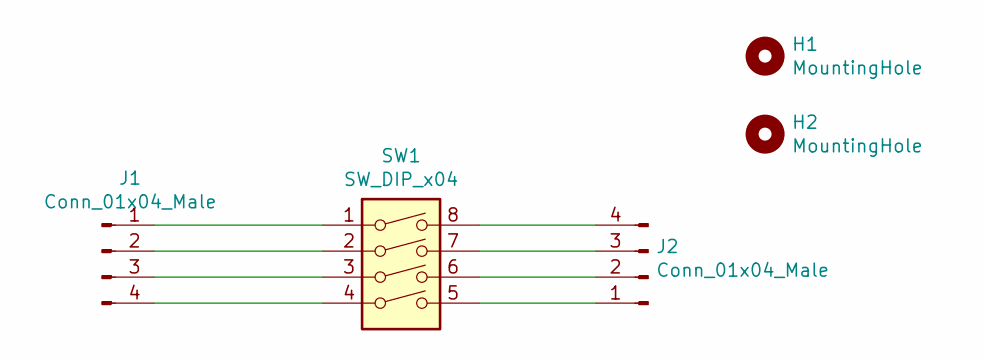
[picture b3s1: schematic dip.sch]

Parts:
H1, H2: MountingHole; MountingHole_2.5mm
J1, J2: Conn_01x04_Male; PinHeader_1x04_P1.27mm_Vertical
SW1: SW_DIP_x04; DIP-8_W7.62mm

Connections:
unnamed: J1.1, SW1.1
unnamed: J1.2, SW1.2
unnamed: J1.3, SW1.3
unnamed: J1.4, SW1.4
unnamed: J2.1, SW1.5
unnamed: J2.2, SW1.6
unnamed: J2.3, SW1.7
unnamed: J2.4, SW1.8

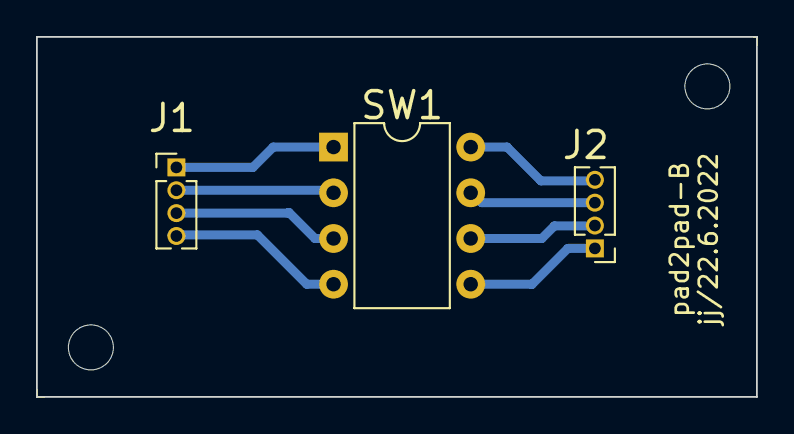
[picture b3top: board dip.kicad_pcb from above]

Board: 2 copper layers, 40.0 x 20.0 mm, 5 parts (0 on the bottom side), 8 nets.

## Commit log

2022-03-01 example
2022-03-01 pic missing
2022-03-01 typos
2022-03-01 doc, doc
2022-03-01 doci
2022-03-01 Cleanup example added
2022-03-01 clenaup exports both
2022-03-01 docker push && pull
2022-03-01 usage
2022-03-01 clarify text, start TAG:2
2022-03-01 doc. docker-tag
2022-03-07 installation instruction, 1/2 sided PCB instructions
2022-03-08 cam PROJECT [PARAMS], usage, --?
2022-03-08 marcus2002/etool:2
2022-03-16 prepare for rel 3
2022-03-18 - User specific CAM -configuration, etoolMac.sh added
2022-03-18 added via to example soic
2022-03-18 Docker tag 4
2022-03-18 doc errorr
2022-03-18 more doc changes
2022-03-18 Docker 4 via missing
2022-03-26 etool.sh image -command
2022-03-27 conde not needed
2022-04-03 Prepapere 5/2022-04-03
2022-04-12 ardrill command, pad2pad&soic projects
2022-04-12 Doc.changes
    Acked-by: jj <jj@santtu.local>
2022-04-12 architecture diagram show image processing
2022-04-21 pathch LIBGL_ALWAYS_INDIRECT=1 to etool.cmd
2022-06-22 help text pcb2gcode changes
2022-07-04 support 02-silk directory
2022-07-04 some typos
2022-07-18 default cam parameters documented
2022-07-18 images added
2022-07-18 latex images removed
2022-07-18 Latex moved to img
2022-07-18 types
2022-07-18 link to cam default
2022-07-18 grep typo
2022-07-18 alignment edges fixed
2022-07-19 overLap calculation fixed, notes.org added
2022-08-19 fixed example: pad2pad, dip, added: milldrill option
2022-08-19 enable milldrill
2022-08-19 Released TAG 7
2022-08-20 snapshot tag 8
2022-08-23 isolation-width + overlap
2022-08-23 Support Kicad 6 Silscreen (Kicad 5 SilkS)
2022-09-06 added USER configuration '3-grooves'
2022-09-06 soic example: added 0603 pad, added track between soic pads
2022-09-07 3-grooves documentation fixed
2022-09-07 header args on github not shown correctly
2022-09-07 header args dir with string
2022-09-07 still header args
2022-11-25 docker-tags function, push 88
2022-11-25 release number bumped up
2023-02-09 fix missing alignment drilling, fixed linux-headers
2023-02-09 commit for TAG=9
2023-02-09 relased TAG=9, snapshot TAG=10
